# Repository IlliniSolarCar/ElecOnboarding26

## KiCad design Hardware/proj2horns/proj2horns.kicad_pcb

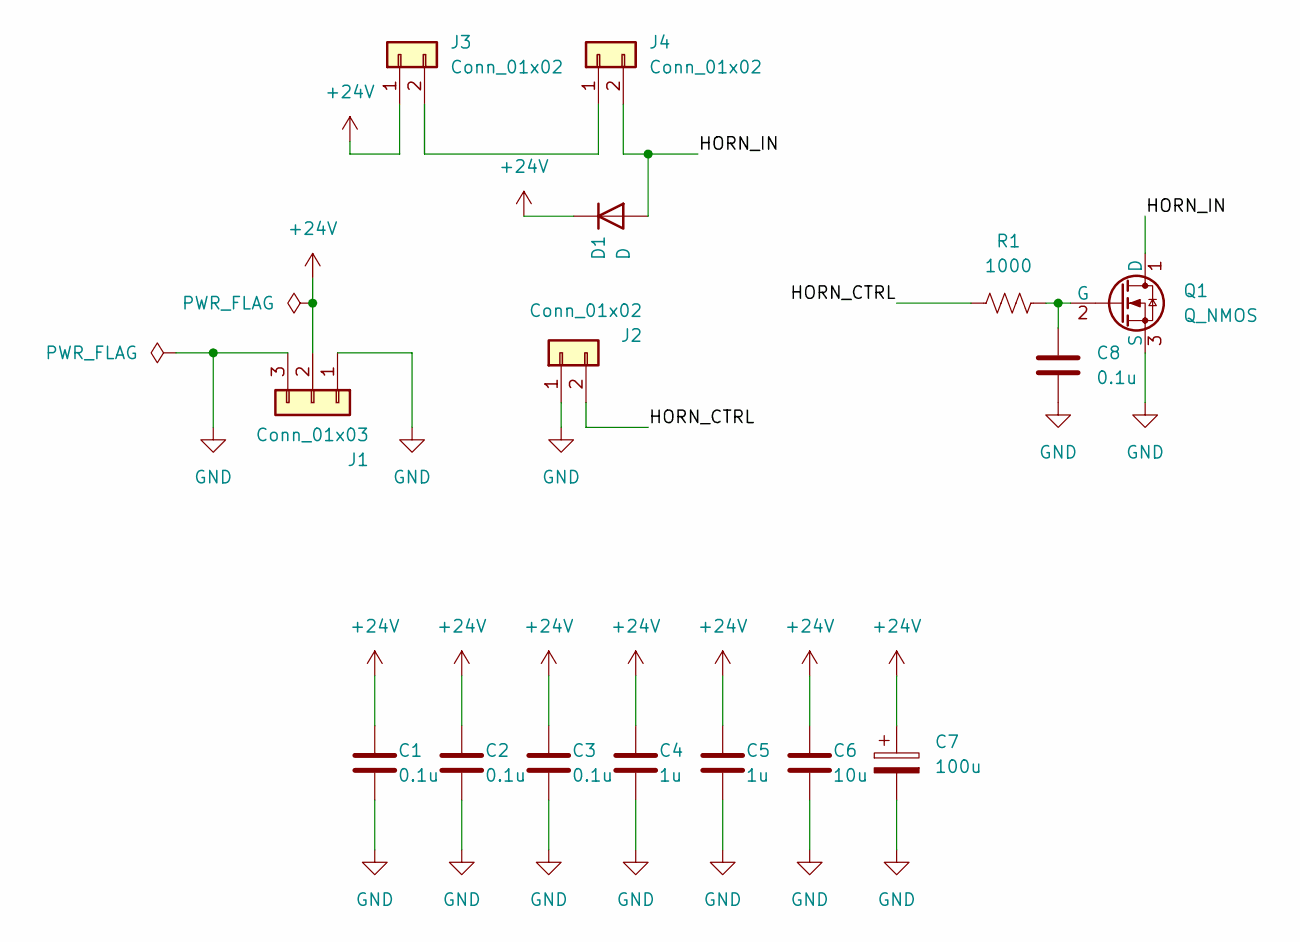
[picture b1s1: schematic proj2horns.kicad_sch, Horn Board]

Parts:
C1, C2, C3, C8: 0.1u; C_0201_0603Metric_Pad0.64x0.40mm_HandSolder
C4, C5: 1u; C_0201_0603Metric_Pad0.64x0.40mm_HandSolder
C6: 10u; C_0201_0603Metric_Pad0.64x0.40mm_HandSolder
C7: 100u; CP_Radial_D13.0mm_P5.08mm
D1: D; D_SMA; MPN ES2DA-13-F
J1: Conn_01x03; Molex_KK-254_AE-6410-03A_1x03_P2.54mm_Vertical; MPN 0022272031
J2, J3, J4: Conn_01x02; Molex_KK-254_AE-6410-02A_1x02_P2.54mm_Vertical; MPN 0022272021
Q1: Q_NMOS; TO-252-2; MPN IRFR010PBF
R1: 1000; R_0603_1608Metric_Pad0.98x0.95mm_HandSolder

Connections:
+24V: C1.1, C2.1, C3.1, C4.1, C5.1, C6.1, C7.1, D1.1 (K), J1.2, J3.1
/HORN_CTRL: J2.2, R1.1
/HORN_IN: D1.2 (A), J4.2, Q1.1 (D)
GND: C1.2, C2.2, C3.2, C4.2, C5.2, C6.2, C7.2, C8.2, J1.1, J1.3, J2.1, Q1.3 (S)
unnamed: J3.2, J4.1
unnamed: C8.1, Q1.2 (G), R1.2

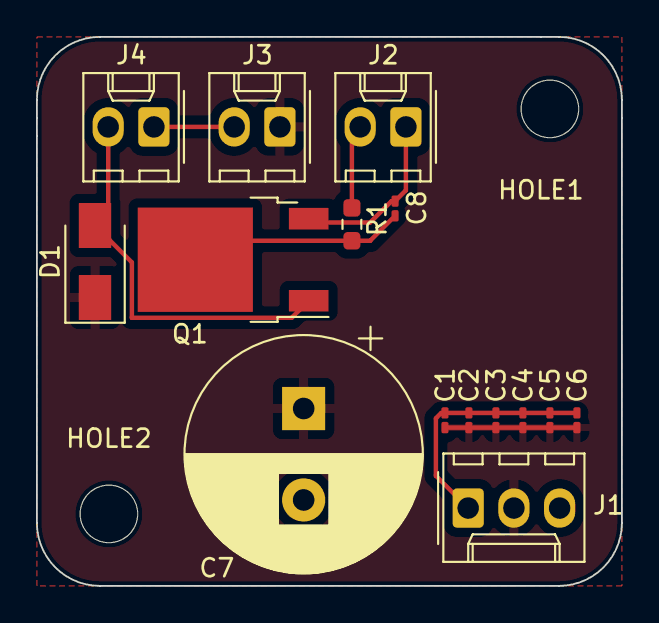
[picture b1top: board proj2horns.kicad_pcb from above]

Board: 2 copper layers, 32.5 x 30.5 mm, 17 parts (0 on the bottom side), 6 nets.

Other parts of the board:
HOLE1, HOLE2: MountingHole_3.2mm_M3

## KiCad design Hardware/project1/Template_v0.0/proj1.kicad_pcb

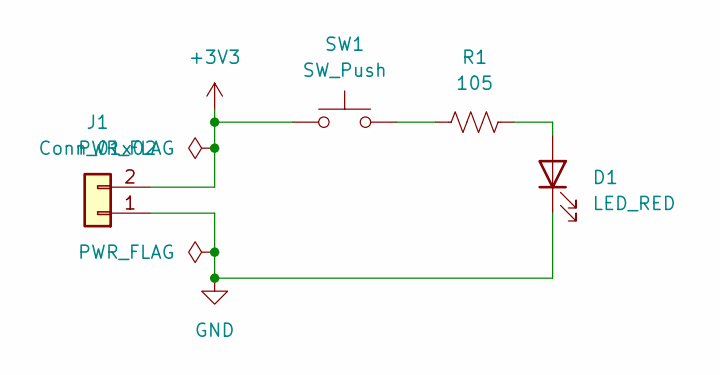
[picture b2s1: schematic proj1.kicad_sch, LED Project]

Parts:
D1: LED_RED; LED_0603_Symbol_on_F.SilkS
J1: Conn_01x02; Molex_KK-254_AE-6410-02A_1x02_P2.54mm_Vertical; MPN 022272021
R1: 105; R_0603_1608Metric_Pad0.98x0.95mm_HandSolder
SW1: SW_Push; SW_DIP_SPSTx01_Slide_6.7x4.1mm_W8.61mm_P2.54mm_LowProfile; MPN 1825910-6

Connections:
+3V3: J1.2, SW1.1
GND: D1.1 (K), J1.1
unnamed: D1.2 (A), R1.2
unnamed: R1.1, SW1.2

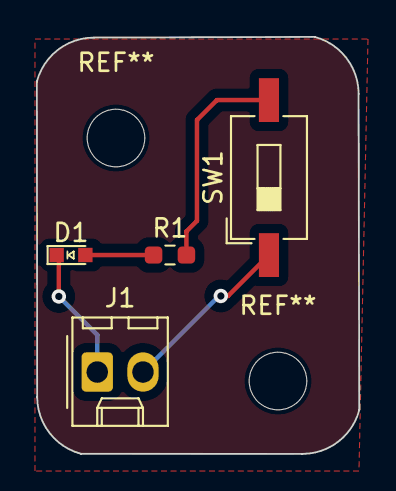
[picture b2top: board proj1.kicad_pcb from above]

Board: 2 copper layers, 17.9 x 23.2 mm, 4 parts (0 on the bottom side), 4 nets.

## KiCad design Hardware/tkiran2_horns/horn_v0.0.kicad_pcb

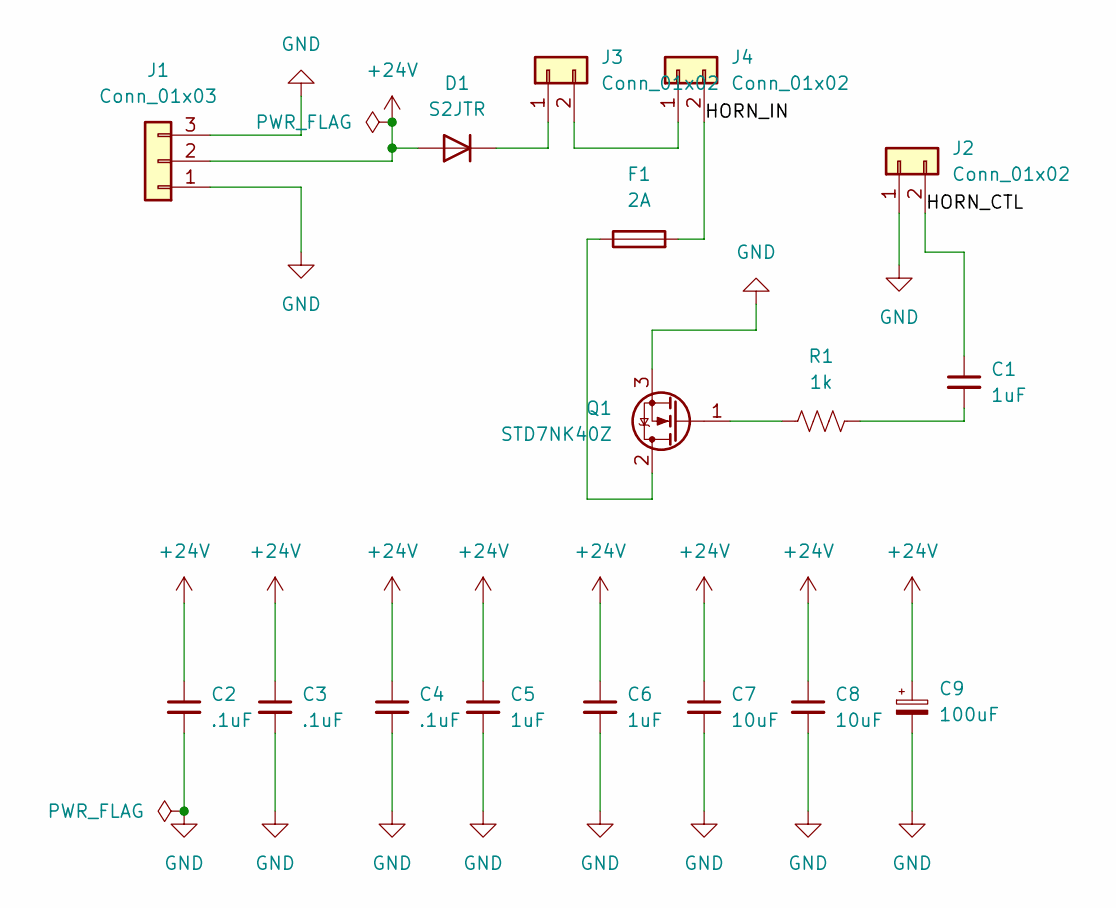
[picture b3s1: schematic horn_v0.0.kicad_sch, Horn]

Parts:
C1, C5, C6: 1uF; C_0603_1608Metric_Pad1.08x0.95mm_HandSolder
C2, C3, C4: .1uF; C_0603_1608Metric_Pad1.08x0.95mm_HandSolder
C7, C8: 10uF; C_0603_1608Metric_Pad1.08x0.95mm_HandSolder
C9: 100uF; C_Elec_5x5.8
D1: S2JTR; D_SMB
F1: 2A; Fuse_0603_1608Metric_Pad1.05x0.95mm_HandSolder
J1: Conn_01x03; JST_EH_B3B-EH-A_1x03_P2.50mm_Vertical
J2, J3, J4: Conn_01x02; JST_EH_B2B-EH-A_1x02_P2.50mm_Vertical
Q1: STD7NK40Z; TO-252-2
R1: 1k; R_0201_0603Metric_Pad0.64x0.40mm_HandSolder

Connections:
+24V: C2.1, C3.1, C4.1, C5.1, C6.1, C7.1, C8.1, C9.1, D1.2 (A), J1.2
/HORN_CTL: C1.1, J2.2
/HORN_IN: F1.2, J4.2
GND: C2.2, C3.2, C4.2, C5.2, C6.2, C7.2, C8.2, C9.2, J1.1, J1.3, J2.1, Q1.3 (S)
unnamed: C1.2, R1.2
unnamed: D1.1 (K), J3.1
unnamed: J3.2, J4.1
unnamed: F1.1, Q1.2 (D)
unnamed: Q1.1 (G), R1.1

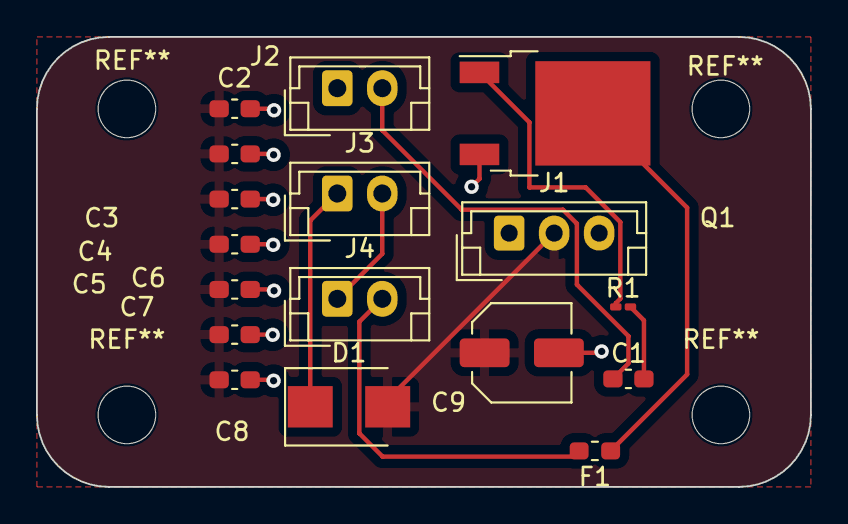
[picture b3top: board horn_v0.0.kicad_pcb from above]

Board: 2 copper layers, 43.0 x 25.0 mm, 17 parts (0 on the bottom side), 9 nets.

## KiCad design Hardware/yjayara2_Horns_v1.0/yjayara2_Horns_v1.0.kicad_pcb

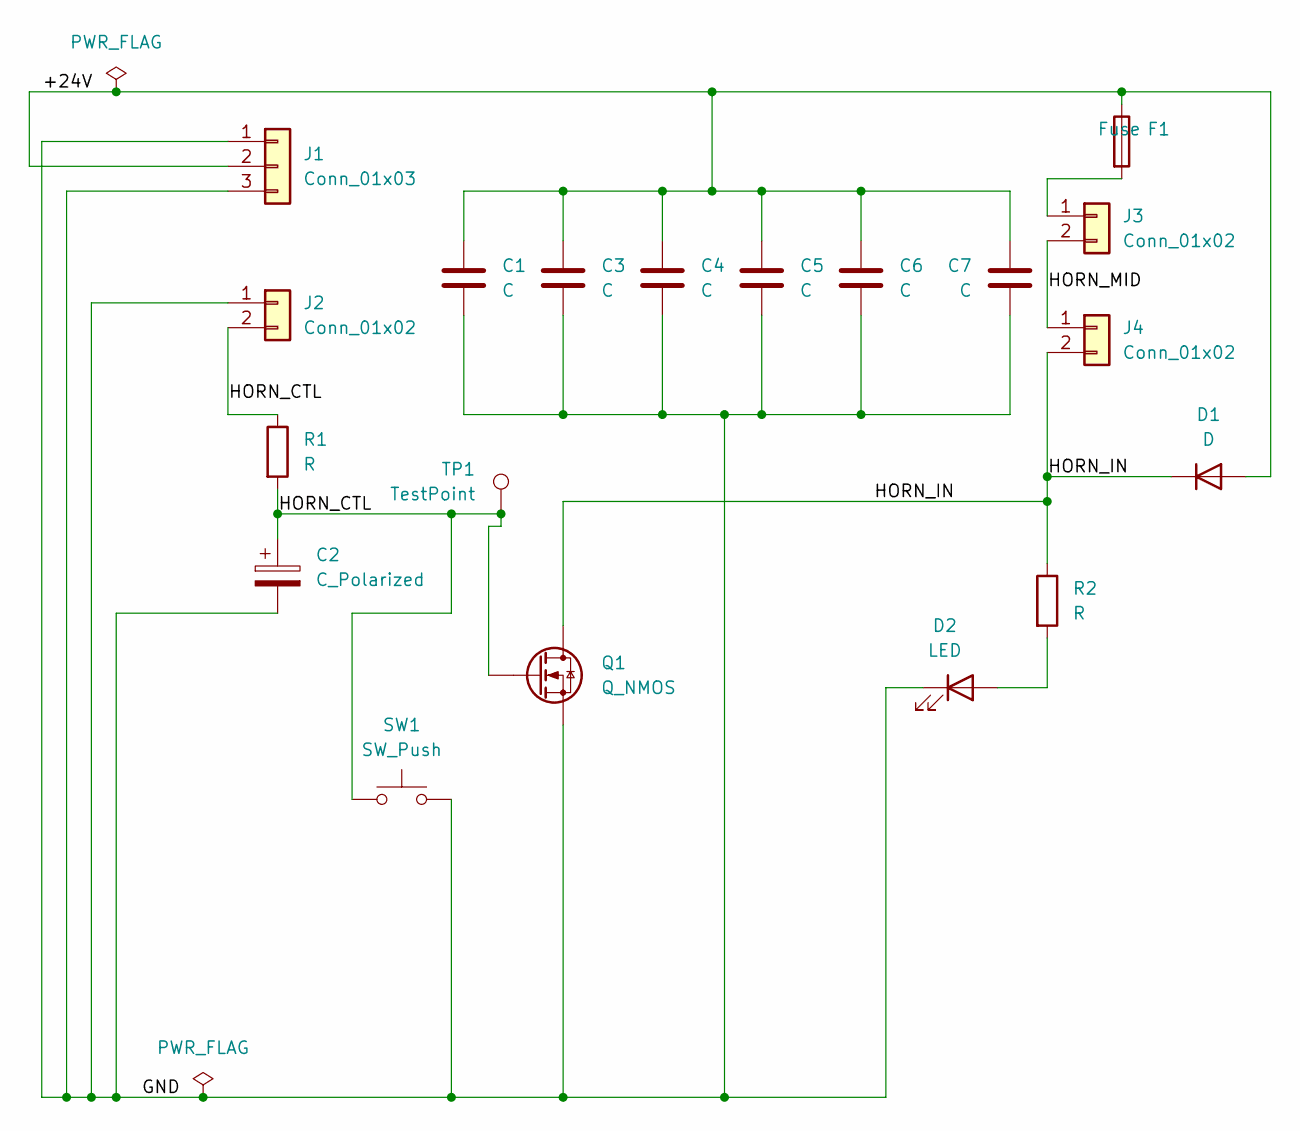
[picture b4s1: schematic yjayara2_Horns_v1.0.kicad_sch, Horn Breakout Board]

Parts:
C1, C3, C4, C5, C6, C7: C; C_0805_2012Metric
C2: C_Polarized; CP_Radial_D5.0mm_P2.00mm
D1: D; D_SMA
D2: LED; LED_D5.0mm
F1: Fuse; Fuseholder_Cylinder-5x20mm_Bulgin_FX0456_Vertical_Closed
J1: Conn_01x03; PinHeader_1x03_P2.54mm_Vertical
J2, J3, J4: Conn_01x02; PinHeader_1x02_P2.54mm_Vertical
Q1: Q_NMOS; TO-252-2_GDS
R1, R2: R; R_0805_2012Metric
SW1: SW_Push; SW_PUSH_6mm
TP1: TestPoint; TestPoint_Pad_D1.0mm

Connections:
/+24V: C1.1, C3.1, C4.1, C5.1, C6.1, C7.1, D1.2 (A), F1.1, J1.2
/GND: C1.2, C2.2, C3.2, C4.2, C5.2, C6.2, C7.2, D2.1 (K), J1.1, J1.3, J2.1, Q1.S, SW1.1
/HORN_CTL: C2.1, J2.2, Q1.G, R1.1, R1.2, SW1.2, TP1.1
/HORN_IN: D1.1 (K), J4.2, Q1.D, R2.1
/HORN_MID: J3.2, J4.1
unnamed: D2.2 (A), R2.2
unnamed: F1.2, J3.1

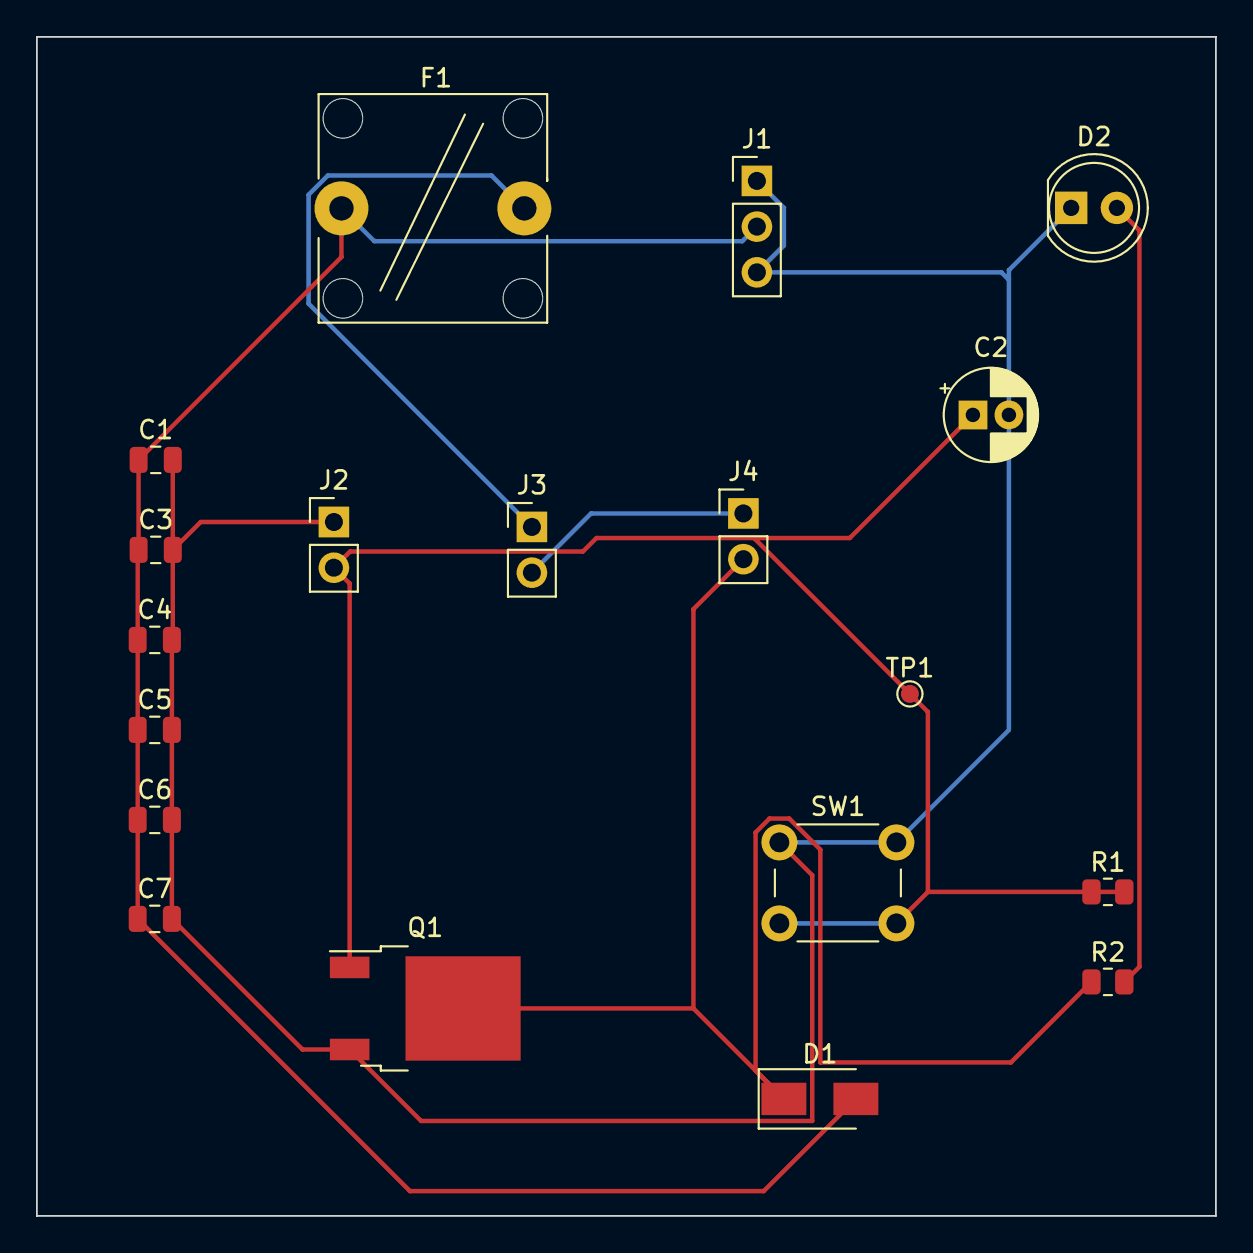
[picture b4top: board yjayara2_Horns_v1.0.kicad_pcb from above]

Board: 2 copper layers, 65.5 x 65.5 mm, 19 parts (0 on the bottom side), 7 nets.
